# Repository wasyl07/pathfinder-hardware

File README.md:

# pathfinder-hardware
Pathfinder project created in Kicad

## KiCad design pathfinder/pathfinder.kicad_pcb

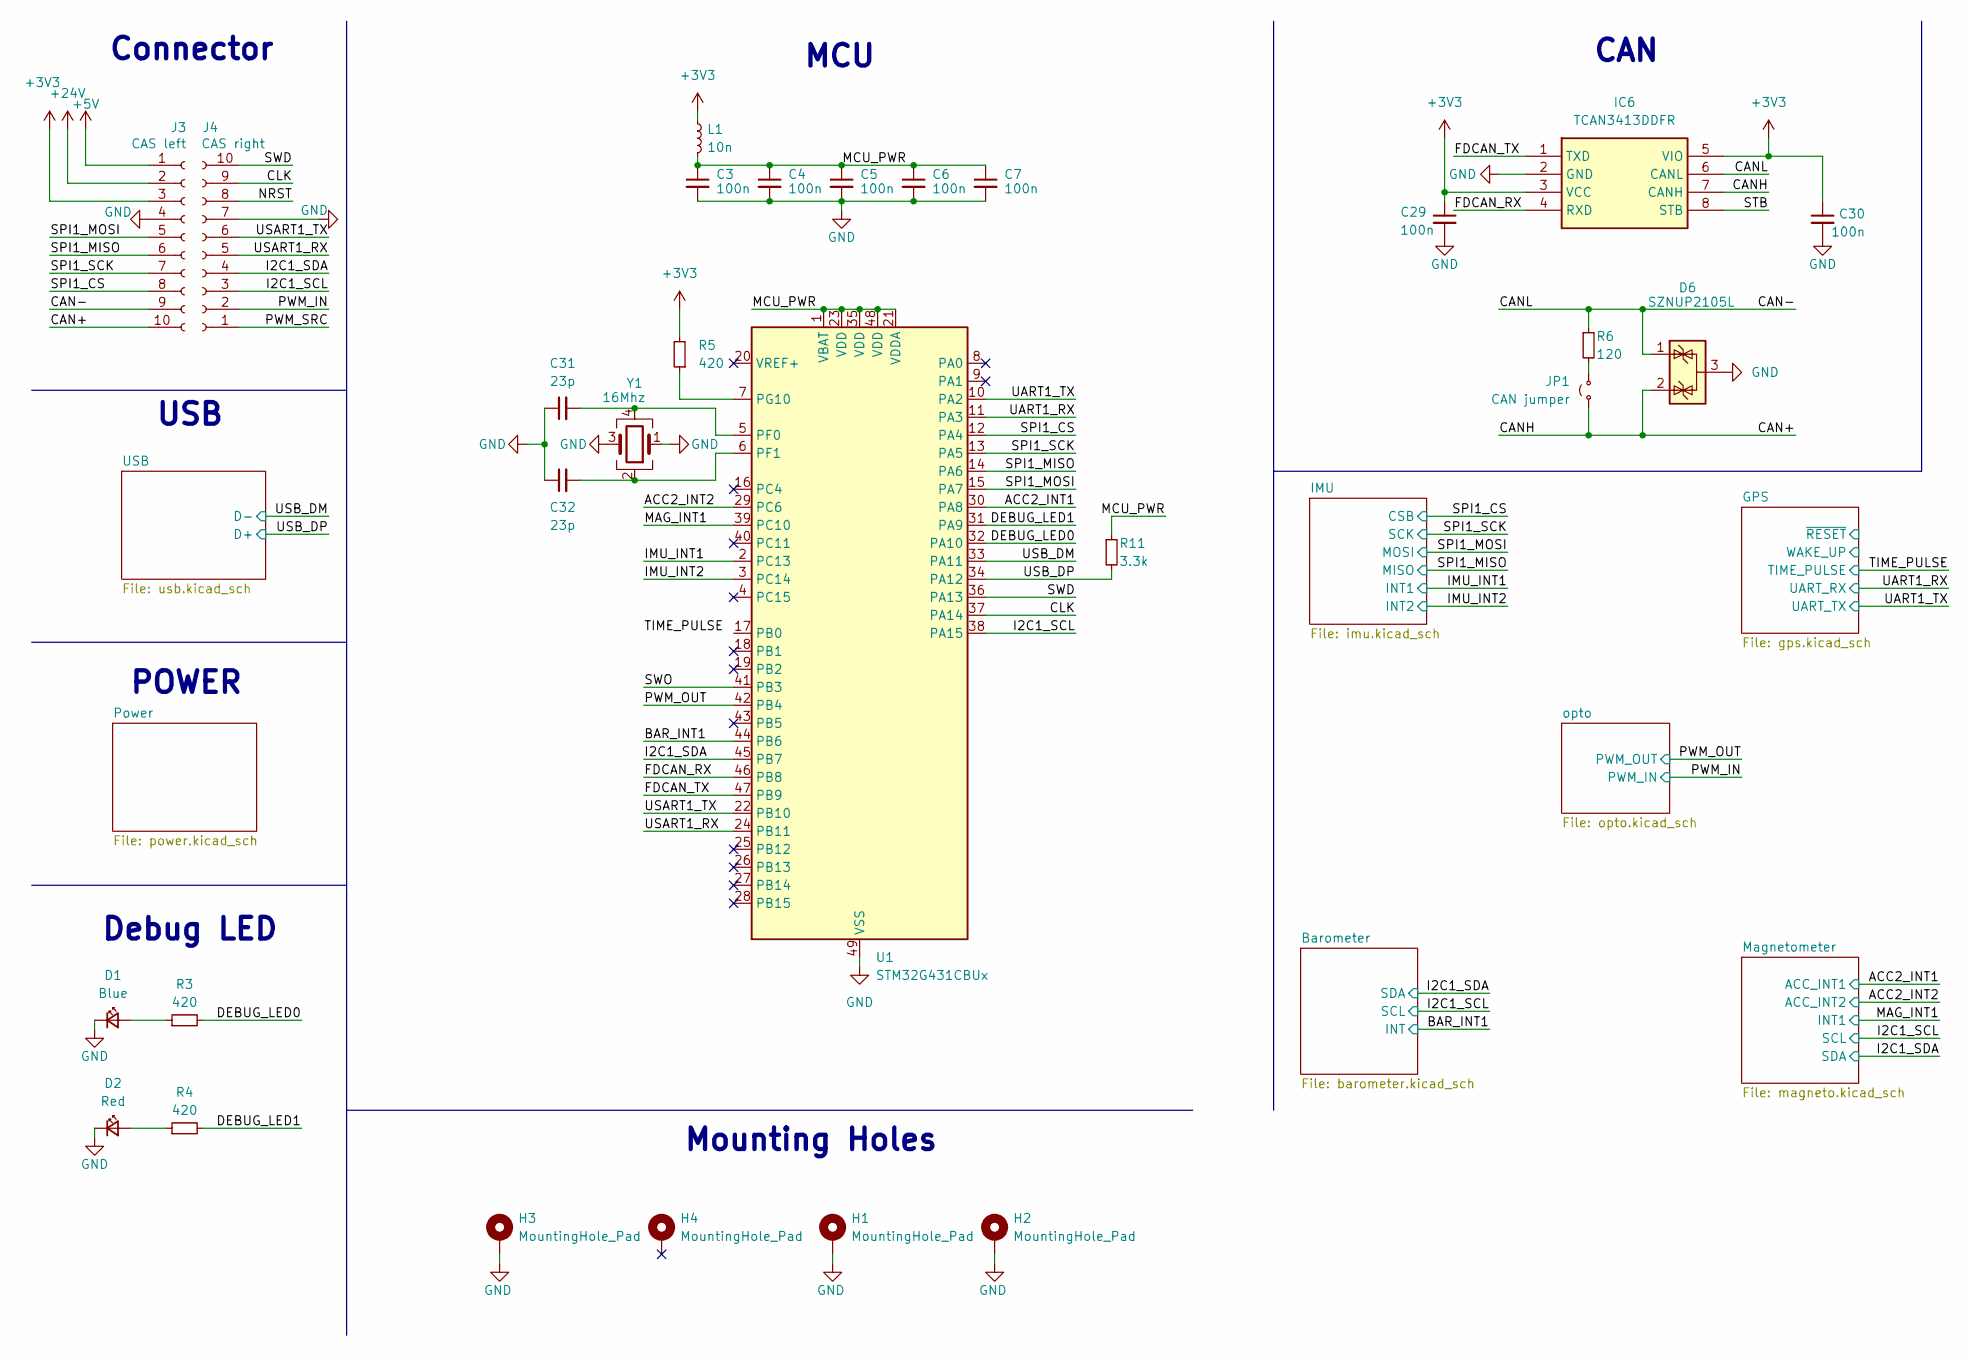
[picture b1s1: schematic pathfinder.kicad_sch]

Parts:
C3, C4, C5, C6, C7, C29, C30: 100n; C_0402_1005Metric_Pad0.74x0.62mm_HandSolder
C31, C32: 23p; C_0402_1005Metric_Pad0.74x0.62mm_HandSolder
D1: Blue; D_0402_1005Metric_Pad0.77x0.64mm_HandSolder
D2: Red; D_0402_1005Metric_Pad0.77x0.64mm_HandSolder
D6: SZNUP2105L; SOT-23
H1, H2, H3, H4: MountingHole_Pad; MountingHole_2.2mm_M2_ISO7380_Pad_TopBottom
IC6: TCAN3413DDFR; SOT65P280X110-8N; Manufacturer_Part_Number TCAN3413DDFR; Mouser Part Number 595-TCAN3413DDFR
J3: CAS left; PinSocket_1x10_P2.54mm_Vertical
J4: CAS right; PinSocket_1x10_P2.54mm_Vertical
JP1: CAN jumper; SolderJumper-2_P1.3mm_Open_RoundedPad1.0x1.5mm
L1: 10n; L_0603_1608Metric_Pad1.05x0.95mm_HandSolder
R3, R4, R5: 420; R_0402_1005Metric_Pad0.72x0.64mm_HandSolder
R6: 120; R_0402_1005Metric_Pad0.72x0.64mm_HandSolder
R11: 3.3k; R_0402_1005Metric_Pad0.72x0.64mm_HandSolder
U1: STM32G431CBUx; QFN-48-1EP_7x7mm_P0.5mm_EP5.6x5.6mm
Y1: 16Mhz; Crystal_SMD_2016-4Pin_2.0x1.6mm

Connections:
+3V3: C29.1, C30.1, IC6.3 (VCC), IC6.5 (VIO), J3.3, L1.1, R5.2; also elsewhere on the board
+5V: J3.1; also elsewhere on the board
+24V: J3.2; also elsewhere on the board
/ACC2_INT1: U1.30 (PA8); also elsewhere on the board
/ACC2_INT2: U1.29 (PC6); also elsewhere on the board
/BAR_INT1: U1.44 (PB6); also elsewhere on the board
/CAN+: D6.2 (K), IC6.7 (CANH), J3.10, JP1.1 (A)
/CAN-: D6.1 (K), IC6.6 (CANL), J3.9, R6.1
/CLK: J4.9, U1.37 (PA14)
/DEBUG_LED0: R3.2, U1.32 (PA10)
/DEBUG_LED1: R4.2, U1.31 (PA9)
/FDCAN_RX: IC6.4 (RXD), U1.46 (PB8)
/FDCAN_TX: IC6.1 (TXD), U1.47 (PB9)
/I2C1_SCL: J4.3, U1.38 (PA15); also elsewhere on the board
/I2C1_SDA: J4.4, U1.45 (PB7); also elsewhere on the board
/IMU_INT1: U1.2 (PC13); also elsewhere on the board
/IMU_INT2: U1.3 (PC14); also elsewhere on the board
/MAG_INT1: U1.39 (PC10); also elsewhere on the board
/MCU_PWR: C3.1, C4.1, C5.1, C6.1, C7.1, L1.2, R11.1, U1.1 (VBAT), U1.21 (VDDA), U1.23 (VDD), U1.35 (VDD), U1.48 (VDD)
/NRST: J4.8
/PWM_IN: J4.2; also elsewhere on the board
/PWM_OUT: U1.42 (PB4); also elsewhere on the board
/PWM_SRC: J4.1
/SPI1_CS: J3.8, U1.12 (PA4); also elsewhere on the board
/SPI1_MISO: J3.6, U1.14 (PA6); also elsewhere on the board
/SPI1_MOSI: J3.5, U1.15 (PA7); also elsewhere on the board
/SPI1_SCK: J3.7, U1.13 (PA5); also elsewhere on the board
/STB: IC6.8 (STB)
/SWD: J4.10, U1.36 (PA13)
/SWO: U1.41 (PB3)
/UART1_RX: U1.11 (PA3); also elsewhere on the board
/UART1_TX: U1.10 (PA2); also elsewhere on the board
/USART1_RX: J4.5, U1.24 (PB11)
/USART1_TX: J4.6, U1.22 (PB10)
/USB_DM: U1.33 (PA11); also elsewhere on the board
/USB_DP: R11.2, U1.34 (PA12); also elsewhere on the board
GND: C3.2, C4.2, C5.2, C6.2, C7.2, C29.2, C30.2, C31.1, C32.1, D1.1 (K), D2.1 (K), D6.3 (A), H1.1, H2.1, H3.1, IC6.2 (GND), J3.4, J4.7, U1.49 (VSS), Y1.1, Y1.3; also elsewhere on the board
unnamed: D1.2 (A), R3.1
unnamed: D2.2 (A), R4.1
unnamed: JP1.2 (B), R6.2
unnamed: C31.2, U1.5 (PF0), Y1.4
unnamed: C32.2, U1.6 (PF1), Y1.2
unnamed: R5.1, U1.7 (PG10)

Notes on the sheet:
POWER
CAN
Mounting Holes
USB
Debug LED
MCU
Connector

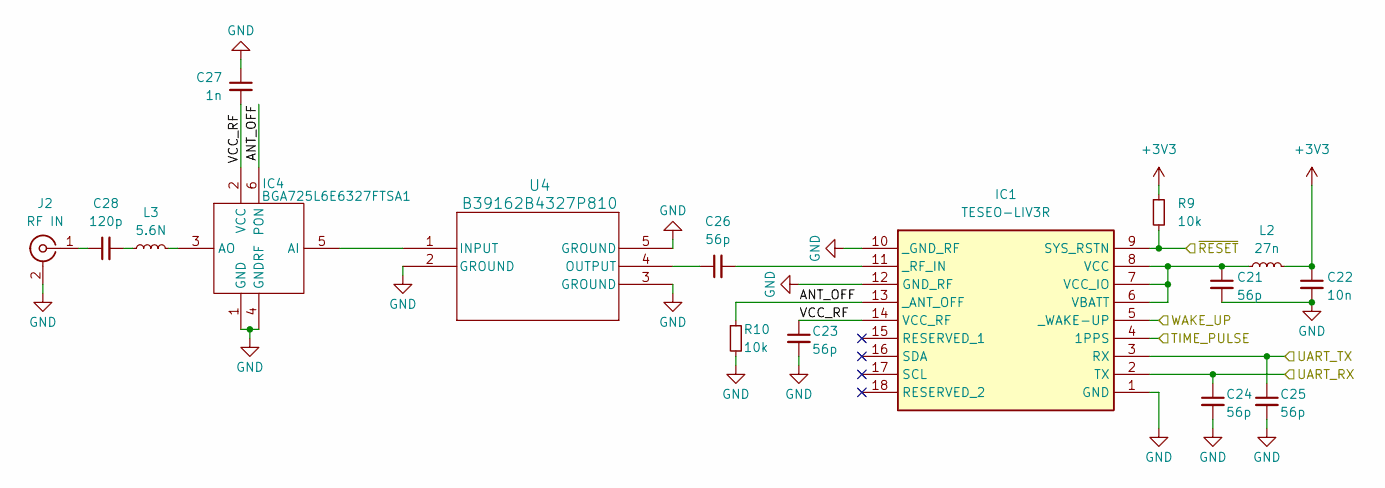
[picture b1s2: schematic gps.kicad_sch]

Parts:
C21, C23, C24, C25, C26: 56p; C_0402_1005Metric_Pad0.74x0.62mm_HandSolder
C22: 10n; C_0402_1005Metric_Pad0.74x0.62mm_HandSolder
C27: 1n; C_0402_1005Metric_Pad0.74x0.62mm_HandSolder
C28: 120p; C_0402_1005Metric_Pad0.74x0.62mm_HandSolder
IC1: TESEO-LIV3R; TESEOLIV3R; Manufacturer_Part_Number TESEO-LIV3R; Mouser Part Number 511-TESEO-LIV3R
IC4: BGA725L6E6327FTSA1; BGS12SN6E6327XTSA1; Manufacturer_Part_Number BGA725L6E6327FTSA1; Mouser Part Number 726-BGA725L6E6327FTS
J2: RF IN; CONUFL001SMDT
L2: 27n; L_0603_1608Metric_Pad1.05x0.95mm_HandSolder
L3: 5.6N; L_0603_1608Metric_Pad1.05x0.95mm_HandSolder
R9, R10: 10k; R_0402_1005Metric_Pad0.72x0.64mm_HandSolder
U4: B39162B4327P810; B39162B4327P810_TDK

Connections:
+3V3: C22.1, L2.2, R9.1; also elsewhere on the board
/GPS/ANT_OFF: IC1.13 (_ANT_OFF), IC4.6 (PON), R10.1
/GPS/VCC_RF: C23.1, C27.2, IC1.14 (VCC_RF), IC4.2 (VCC)
/GPS/WAKE_UP: IC1.5 (_WAKE-UP)
/GPS/~RESET: IC1.9 (SYS_RSTN), R9.2
/TIME_PULSE: IC1.4 (1PPS)
/UART1_RX: C24.1, IC1.2 (TX); also elsewhere on the board
/UART1_TX: C25.1, IC1.3 (RX); also elsewhere on the board
GND: C21.2, C22.2, C23.2, C24.2, C25.2, C27.1, IC1.1 (GND), IC1.10 (_GND_RF), IC1.12 (GND_RF), IC4.1 (GND), IC4.4 (GNDRF), J2.2 (Ext), R10.2, U4.2 (GROUND), U4.3 (GROUND), U4.5 (GROUND); also elsewhere on the board
unnamed: C28.2, L3.1
unnamed: C21.1, IC1.6 (VBATT), IC1.7 (VCC_IO), IC1.8 (VCC), L2.1
unnamed: C26.2, IC1.11 (_RF_IN)
unnamed: IC4.5 (AI), U4.1 (INPUT)
unnamed: IC4.3 (AO), L3.2
unnamed: C28.1, J2.1 (In)
unnamed: C26.1, U4.4 (OUTPUT)

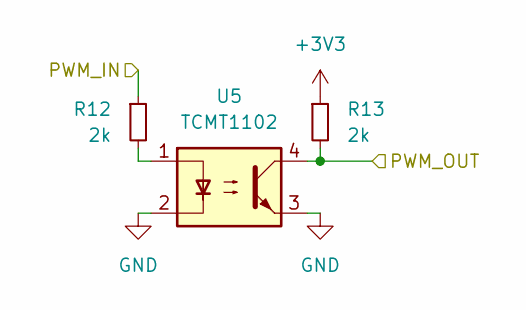
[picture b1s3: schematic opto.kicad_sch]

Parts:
R12, R13: 2k; R_0402_1005Metric_Pad0.72x0.64mm_HandSolder
U5: TCMT1102; SOP-4_4.4x2.6mm_P1.27mm

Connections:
+3V3: R13.1; also elsewhere on the board
/PWM_IN: R12.1; also elsewhere on the board
/PWM_OUT: R13.2, U5.4; also elsewhere on the board
GND: U5.2, U5.3; also elsewhere on the board
unnamed: R12.2, U5.1

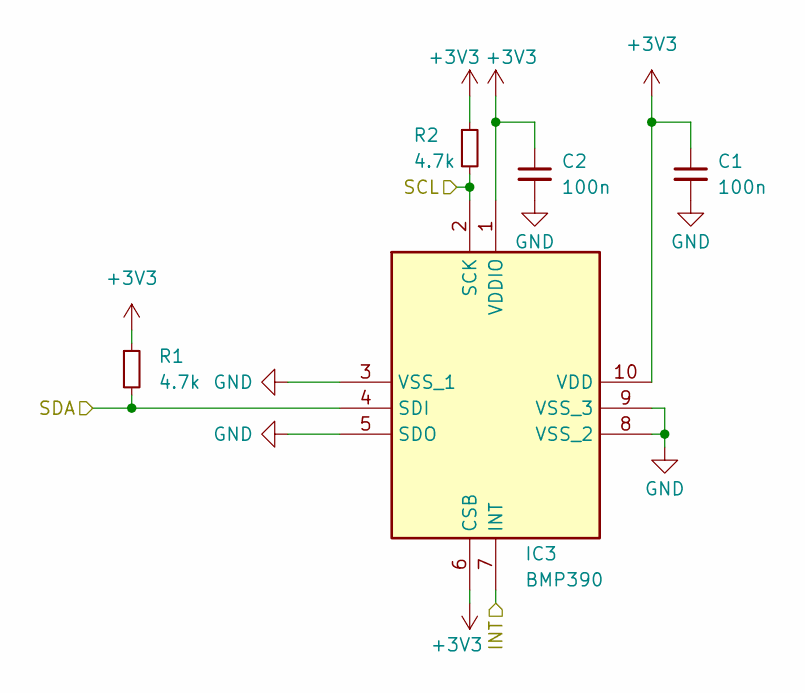
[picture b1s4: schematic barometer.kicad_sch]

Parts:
C1, C2: 100n; C_0402_1005Metric_Pad0.74x0.62mm_HandSolder
IC3: BMP390; Manufacturer_Part_Number BMP390; Mouser Part Number 262-BMP390
R1, R2: 4.7k; R_0402_1005Metric_Pad0.72x0.64mm_HandSolder

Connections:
+3V3: C1.1, C2.1, IC3.1 (VDDIO), IC3.6 (CSB), IC3.10 (VDD), R1.1, R2.1; also elsewhere on the board
/BAR_INT1: IC3.7 (INT); also elsewhere on the board
/I2C1_SCL: IC3.2 (SCK), R2.2; also elsewhere on the board
/I2C1_SDA: IC3.4 (SDI), R1.2; also elsewhere on the board
GND: C1.2, C2.2, IC3.3 (VSS_1), IC3.5 (SDO), IC3.8 (VSS_2), IC3.9 (VSS_3); also elsewhere on the board

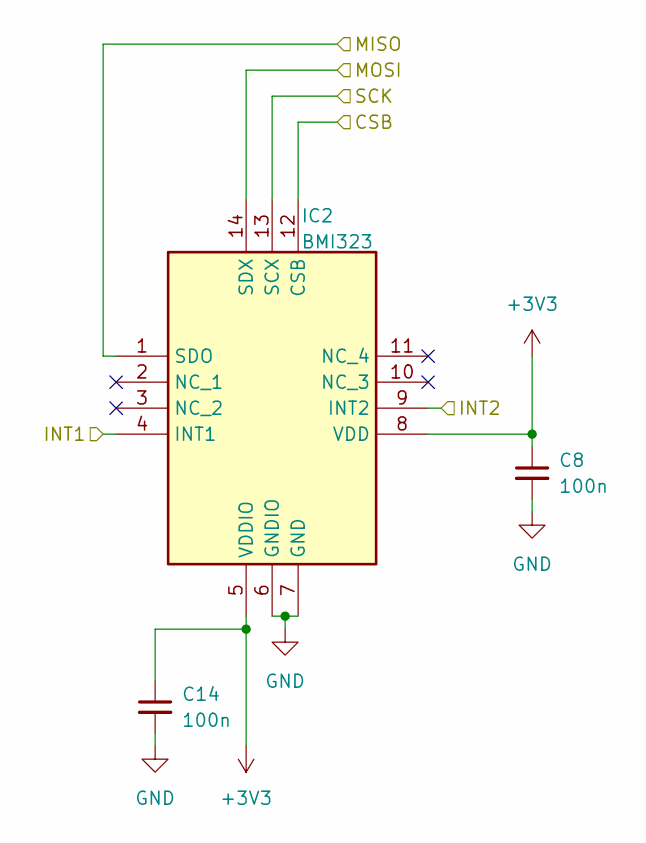
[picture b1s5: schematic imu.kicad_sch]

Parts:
C8, C14: 100n; C_0402_1005Metric_Pad0.74x0.62mm_HandSolder
IC2: BMI323; Manufacturer_Part_Number BMI323; Mouser Part Number 262-BMI323

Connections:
+3V3: C8.1, C14.1, IC2.5 (VDDIO), IC2.8 (VDD); also elsewhere on the board
/IMU_INT1: IC2.4 (INT1); also elsewhere on the board
/IMU_INT2: IC2.9 (INT2); also elsewhere on the board
/SPI1_CS: IC2.12 (CSB); also elsewhere on the board
/SPI1_MISO: IC2.1 (SDO); also elsewhere on the board
/SPI1_MOSI: IC2.14 (SDX); also elsewhere on the board
/SPI1_SCK: IC2.13 (SCX); also elsewhere on the board
GND: C8.2, C14.2, IC2.6 (GNDIO), IC2.7 (GND); also elsewhere on the board

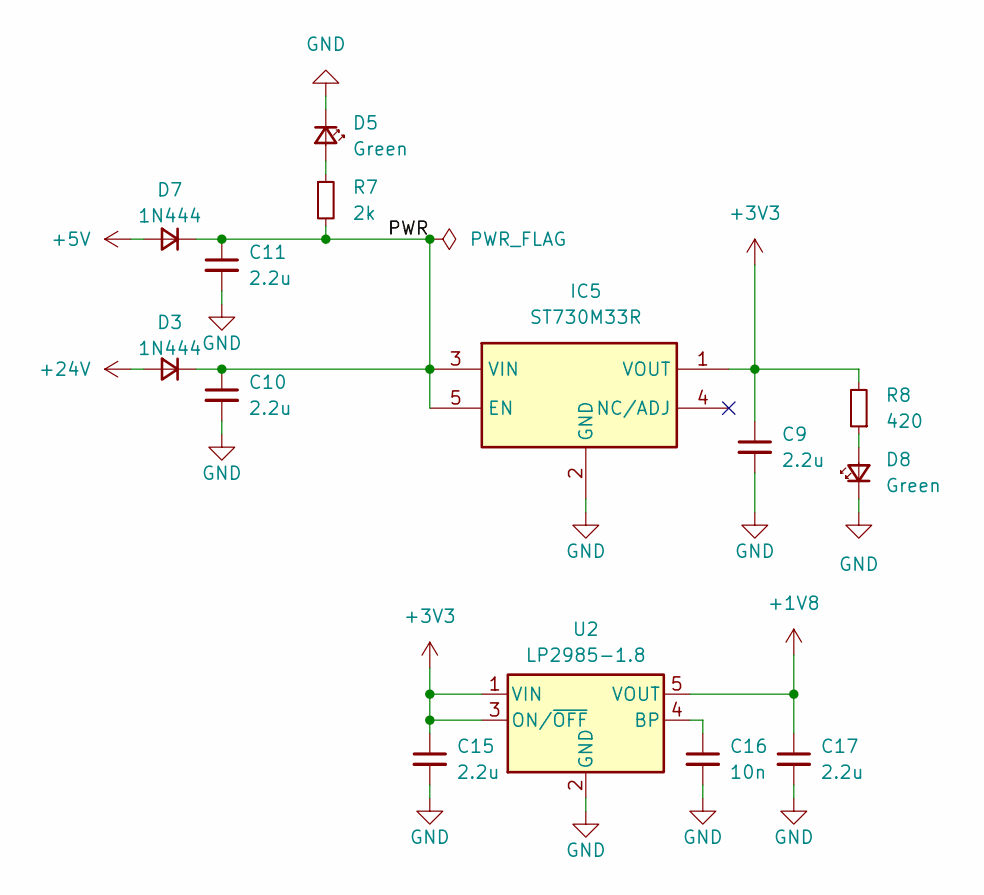
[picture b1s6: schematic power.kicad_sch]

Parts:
C9, C10, C11, C15, C17: 2.2u; C_0402_1005Metric_Pad0.74x0.62mm_HandSolder
C16: 10n; C_0402_1005Metric_Pad0.74x0.62mm_HandSolder
D3, D7: 1N444; D_0603_1608Metric_Pad1.05x0.95mm_HandSolder
D5, D8: Green; D_0402_1005Metric_Pad0.77x0.64mm_HandSolder
IC5: ST730M33R; SOT95P280X145-5N; Manufacturer_Part_Number ST730M33R; Mouser Part Number 511-ST730M33R
R7: 2k; R_0402_1005Metric_Pad0.72x0.64mm_HandSolder
R8: 420; R_0402_1005Metric_Pad0.72x0.64mm_HandSolder
U2: LP2985-1.8; SOT-23-5

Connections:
+1V8: C17.1, U2.5 (VOUT); also elsewhere on the board
+3V3: C9.1, C15.1, IC5.1 (VOUT), R8.2, U2.1 (VIN), U2.3 (ON/~OFF); also elsewhere on the board
+5V: D7.2 (A); also elsewhere on the board
+24V: D3.2 (A); also elsewhere on the board
/Power/PWR: C10.1, C11.1, D3.1 (K), D7.1 (K), IC5.3 (VIN), IC5.5 (EN), R7.2
GND: C9.2, C10.2, C11.2, C15.2, C16.2, C17.2, D5.1 (K), D8.1 (K), IC5.2 (GND), U2.2 (GND); also elsewhere on the board
unnamed: D5.2 (A), R7.1
unnamed: D8.2 (A), R8.1
unnamed: C16.1, U2.4 (BP)

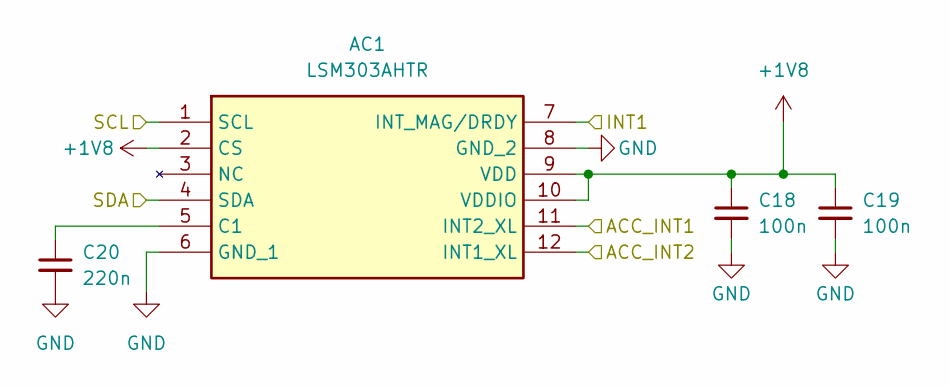
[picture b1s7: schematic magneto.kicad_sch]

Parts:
AC1: LSM303AHTR; LGA-12; Manufacturer_Part_Number LSM303AHTR; Mouser Part Number 511-LSM303AHTR
C18, C19: 100n; C_0402_1005Metric_Pad0.74x0.62mm_HandSolder
C20: 220n; C_0402_1005Metric_Pad0.74x0.62mm_HandSolder

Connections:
+1V8: AC1.2 (CS), AC1.9 (VDD), AC1.10 (VDDIO), C18.1, C19.1; also elsewhere on the board
/ACC2_INT1: AC1.11 (INT2_XL); also elsewhere on the board
/ACC2_INT2: AC1.12 (INT1_XL); also elsewhere on the board
/I2C1_SCL: AC1.1 (SCL); also elsewhere on the board
/I2C1_SDA: AC1.4 (SDA); also elsewhere on the board
/MAG_INT1: AC1.7 (INT_MAG/DRDY); also elsewhere on the board
GND: AC1.6 (GND_1), AC1.8 (GND_2), C18.2, C19.2, C20.2; also elsewhere on the board
unnamed: AC1.5 (C1), C20.1

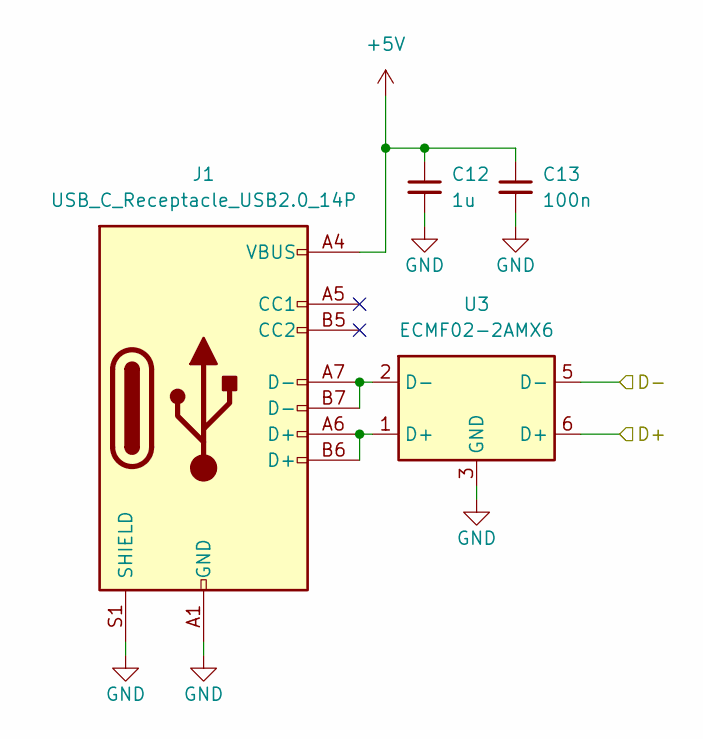
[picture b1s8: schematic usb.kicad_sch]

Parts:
C12: 1u; C_0402_1005Metric_Pad0.74x0.62mm_HandSolder
C13: 100n; C_0402_1005Metric_Pad0.74x0.62mm_HandSolder
J1: USB_C_Receptacle_USB2.0_14P; USB_C_Receptacle_GCT_USB4105-xx-A_16P_TopMnt_Horizontal
U3: ECMF02-2AMX6; ST_UQFN-6L_1.5x1.7mm_P0.5mm

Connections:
+5V: C12.1, C13.1, J1.A4 (VBUS), J1.A9 (VBUS), J1.B4 (VBUS), J1.B9 (VBUS); also elsewhere on the board
/USB_DM: U3.5 (D-); also elsewhere on the board
/USB_DP: U3.6 (D+); also elsewhere on the board
GND: C12.2, C13.2, J1.A1 (GND), J1.A12 (GND), J1.B1 (GND), J1.B12 (GND), J1.S1 (SHIELD), U3.3 (GND); also elsewhere on the board
unnamed: J1.A6 (D+), J1.B6 (D+), U3.1 (D+)
unnamed: J1.A7 (D-), J1.B7 (D-), U3.2 (D-)

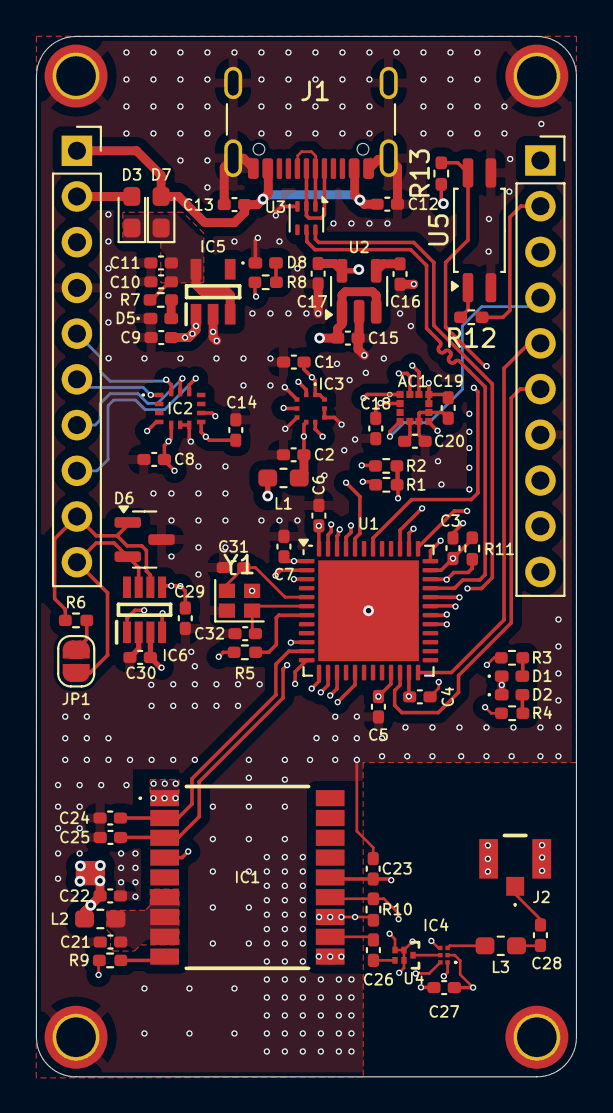
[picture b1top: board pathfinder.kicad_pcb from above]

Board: 4 copper layers, 30.0 x 57.8 mm, 77 parts (0 on the bottom side), 58 nets.

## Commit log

2024-12-28 Start components layout
2025-01-01 Board finished
2025-01-02 Add optocoupler
2025-01-02 change 1v8 ldo power supply
2025-01-02 update gitignore
